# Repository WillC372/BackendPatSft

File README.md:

# Aqua Assistant AI · Backend

API REST principal de **Aqua Assistant AI**, un sistema de monitoreo de pH del agua: autenticación, perfiles de agua, mediciones, **lectura del medidor físico** (USB o Bluetooth SPP), lugares, cuidado del agua, alertas y avisos, pagos y datos oficiales.

El proyecto está en cuatro repositorios:

| Repositorio | Qué es | Dónde corre |
|---|---|---|
| [FrontendPatSft](https://github.com/WillC372/FrontendPatSft) | La aplicación web | Vercel |
| **BackendPatSft** (este) | API principal | Render |
| [AIPatSft](https://github.com/WillC372/AIPatSft) | Servicio de IA: Aqua (chat), diagnóstico, anomalías, predicción, LSTM, Isolation Forest, simulador, agente de informes, informes PDF, lectura de fotos, biblioteca normativa y traducciones | Render |
| [DBPatSft](https://github.com/WillC372/DBPatSft) | Esquema y migraciones de la base de datos | Neon (PostgreSQL) |

Los dos servicios usan la misma base de datos y la misma sesión: el servicio de IA acepta el token que entrega este backend (misma `JWT_SECRET`) y comprueba en la base que la sesión siga abierta. Entre ellos hablan por dos rutas internas protegidas con la clave compartida `INTERNAL_API_KEY`: el servicio de IA envía aquí las mediciones leídas de una foto (para que se validen y generen alertas como cualquier otra) y este backend le pide la traducción de los correos y avisos que todavía no estén en la tabla compartida.

> Frontend: carpeta [`../Frontend`](../Frontend) (repositorio [FrontendPatSft](https://github.com/WillC372/FrontendPatSft)).
>
> Requerimientos funcionales y no funcionales (historias de usuario con criterios de aceptación y MockUps): [FrontendPatSft/docs/Requerimientos.md](https://github.com/WillC372/FrontendPatSft/blob/main/docs/Requerimientos.md).

## Responsabilidades del servidor

- Registrar usuarios, iniciar y cerrar sesión, recuperar contraseñas (JWT + Argon2id).
- Guardar la **foto de perfil**: se recorta en cuadrado, se reduce a 256 px y se vuelve a codificar (se borran los metadatos, como la ubicación). Solo la ve su dueño.
- Guardar el **historial de sesiones**: cada inicio de sesión abre una sesión que agrupa todo lo que el usuario hace hasta cerrarla.
- Mantener las **cuentas de demostración** de los tres botones del inicio de sesión: Usuario, Premium y Administrador.
- Importar **datos oficiales de pH** del Servicio Geológico de EE. UU. (USGS) cada 3 horas y guardarlos aparte de las mediciones de los usuarios.
- Guardar y consultar mediciones con su origen: `REAL` (medidor), `MANUAL` o `PHOTO` (foto leída por el servicio de IA, que la envía a `POST /api/v1/internal/measurements`). El origen `SIMULATED` solo existe en las pruebas automáticas.
- Validar cada lectura (cadena de validación) y clasificarla según el perfil de agua activo.
- Hablar con el medidor por puerto serie: búsqueda, conexión, medición estabilizada, calibración y transmisión en vivo (Server-Sent Events).
- Generar **alertas** al guardar cada medición con reglas fijas: fuera del rango del perfil, **alteración del pH** y valor atípico (`alert/analysis`). El Isolation Forest y el resto de análisis están en el servicio de IA.
- **Datos oficiales del USGS en un lugar** (`place/OfficialDataService`, `POST/DELETE /api/v1/places/{id}/official-data`): carga en un lugar las lecturas reales de una estación del USGS que ya se importan (una por hora, hasta 30 días) con origen `OFFICIAL` («Dato oficial del USGS»), sin alertas ni validación de lecturas nuevas y sin repetir horas ya cargadas. Sirven para ver los análisis con días de datos reales antes de tener mediciones propias; nunca se presentan como mediciones de la persona y se pueden quitar.
- **Alteración del pH** (`PhAlterationRule`): si el pH cambia 0,5 o más frente a cualquier medición de la última hora (también con un medidor que mide cada 10 s y un cambio que crece en varios minutos), o si entra en nivel crítico, se crea la alerta «Alteración del pH en el agua» (`kind` = `PH_ALTERATION`). El mensaje dice si es peligroso según los rangos del perfil (crítico = peligroso) y qué hacer según el tipo de agua (piscina: salir del agua; acuario: los peces corren peligro; agua potable: no tomarla; riego: no regar). El aviso al celular o computador va como urgente (`Urgency: high`), queda en pantalla y vibra; la app hace sonar la alarma y Aqua lo dice en voz alta. La misma alerta no se repite en el mismo lugar durante 30 minutos (salvo que se vuelva peligrosa).
- Separar las mediciones por **lugar** (piscina, acuario, tanque...) y **compartir** un lugar con un código (rol solo ver o ver y medir).
- Guardar **otros parámetros** (cloro libre, alcalinidad, dureza cálcica, ácido cianúrico), **tratamientos**, **recordatorios** e **historial de calibraciones**.
- Enviar **avisos fuera de la app**: Web Push (cifrado RFC 8291 y VAPID RFC 8292 con el JDK, sin dependencias; las claves se crean solas en `app_keys`) y correo, para alertas y recordatorios vencidos.
- Enviar los correos y los avisos en el idioma de cada persona (`i18n/`): las traducciones están en la tabla compartida `ui_translations`, que llena el servicio de IA; lo que falta se le pide a él y, si no responde a tiempo (duerme cuando nadie lo usa), ese texto sale en español.
- Exportar mediciones a CSV. Los informes en PDF los genera el servicio de IA.

## Arquitectura

Monolito modular en capas (controlador → servicio → repositorio), organizado por módulo de negocio. Detalle y diagramas en [`docs/Architecture.md`](docs/Architecture.md). Catálogo de patrones de diseño con su función real y sus pruebas en [`docs/DesignPatterns.md`](docs/DesignPatterns.md).

```
src/main/java/com/aquaassistant/
├── AquaAssistantApplication.java
├── config/         Seguridad, CORS, OpenAPI y propiedades tipadas
├── security/       JWT, filtro de autenticación, limitador de intentos
├── common/         Errores de negocio y manejo centralizado de excepciones
├── audit/          Historial de operaciones, cada una ligada a la sesión en que se hizo
├── user/           Usuarios, autenticación, sesiones (historial), cuentas de demostración, recuperación, preferencias
├── admin/          Administración de usuarios y planes: búsqueda, plan, rol, desactivación, pagos y auditoría
├── profile/        Perfiles de agua, rangos y clasificador de pH
├── measurement/    Mediciones, cadena de validación, filtros (Specification), iterador y observadores
├── device/         Hardware: adaptadores, simulador, fábrica, máquina de estados, comandos, SSE
├── alert/          Alertas: reglas fijas al guardar cada medición (alert/analysis) y avisos
├── i18n/           Idioma de cada persona y traducción de correos y avisos (tabla compartida + servicio de IA)
├── reference/      Datos oficiales del USGS: cliente de su API (Adapter), importador programado y consulta
└── dashboard/      Consulta agregada para la pantalla de inicio
src/main/resources/
└── application.yml
src/test/resources/db/migration/   Copia de las migraciones de DBPatSft para las pruebas (java scripts/SyncMigrations.java ../DBPatSft)
docs/                        Documentación técnica
```

## Convenciones de código

- **Inglés:** nombres de clases, métodos y variables, comentarios y Javadoc, mensajes del log, claves de los datos que recibe la IA y las instrucciones (prompts) de cada capa de IA. Los prompts piden de forma explícita que la IA responda en español.
- **Español:** solo lo que ve el usuario: mensajes de error de la API, textos de informes, PDF y correos, etiquetas y resúmenes de las normas.
- **Nombres de archivo en inglés y en PascalCase**, como `MeasurementService.java`, `docs/DesignPatterns.md` o `knowledge/Guidelines.json`. Las migraciones conservan el prefijo que exige Flyway (`V1__CreateSchema.sql`).
- **Excepciones por convención de las herramientas:** `README.md`, `pom.xml`, `application.yml`, `Dockerfile`, `docker-compose.yml`, `.gitignore` y `.env.example`. Las carpetas de paquetes Java van en minúsculas, como exige Java.

Una base de datos creada antes del cambio de nombre de las migraciones necesita `flyway repair` (o actualizar `flyway_schema_history`) para registrar los nombres y sumas de verificación nuevos; una base nueva no necesita nada.

## Tecnologías

| Componente | Tecnología |
|---|---|
| Lenguaje | Java 21 |
| Framework | Spring Boot 3.4.5 (Web, Data JPA, Security, Validation, Mail, Actuator) |
| Base de datos | PostgreSQL 16 (Neon); el esquema lo aplica el repositorio DBPatSft con Flyway |
| Seguridad | JWT HS256 (jjwt 0.12.6), contraseñas con Argon2id (Bouncy Castle) |
| Hardware | jSerialComm 2.11.0 (USB serie y Bluetooth clásico SPP) |
| Documentación de la API | springdoc-openapi 2.8.6 (Swagger UI) |
| Pruebas | JUnit 5, Mockito, AssertJ, Awaitility, MockMvc, H2 (modo PostgreSQL) |

## Requisitos previos

- JDK 21 y Maven 3.9 o superior.
- PostgreSQL 16 (o Docker para levantarlo).
- Opcional: clave de la API de Anthropic, servidor SMTP y un medidor compatible (ver [`docs/Hardware.md`](docs/Hardware.md)).

## Instalación y ejecución local

1. Crea la base de datos:
   ```bash
   sudo -u postgres psql -c "CREATE USER aquasense WITH PASSWORD 'cambia-esta-clave';"
   sudo -u postgres psql -c "CREATE DATABASE aquasense OWNER aquasense;"
   ```
2. Copia `.env.example` como `.env` y completa al menos `DB_PASSWORD` y `JWT_SECRET` (32 caracteres o más).
3. Exporta las variables y arranca:
   ```bash
   set -a && source .env && set +a
   mvn spring-boot:run
   ```
   o compila el JAR:
   ```bash
   mvn -DskipTests package
   java -jar target/aqua-assistant-backend-1.0.0.jar
   ```
4. Comprueba: `http://localhost:8080/actuator/health` debe responder `{"status":"UP"}`.

Flyway crea las tablas y los cinco perfiles del sistema en el primer arranque; no hay que ejecutar SQL a mano.

### Con Docker

```bash
cp .env.example .env    # completa DB_PASSWORD y JWT_SECRET
docker compose --env-file .env up --build
```

> En Docker el backend no ve los puertos serie del equipo anfitrión. Para usar un medidor real, ejecuta el JAR directamente en el equipo donde está conectado el medidor, o comparte el dispositivo con el contenedor (`devices:` en Compose, solo en Linux).

## Variables de entorno

| Variable | Obligatoria | Descripción |
|---|---|---|
| `DB_URL`, `DB_USER`, `DB_PASSWORD` | Sí | Conexión a PostgreSQL (o `DATABASE_URL` con la cadena de Neon) |
| `AI_SERVICE_URL` | No | Dirección del servicio de IA, para traducir correos y avisos (`http://localhost:8081`) |
| `INTERNAL_API_KEY` | No | Clave que comparten este backend y el servicio de IA para sus llamadas internas (16 caracteres o más, la misma en los dos). Sin ella no se guardan las lecturas por foto |
| `FLYWAY_ENABLED` | No | `false`: el esquema lo aplica DBPatSft. Ponlo en `true` solo para crear una base local vacía con la copia de las pruebas |
| `JWT_SECRET` | Sí | Clave de firma de tokens, mínimo 32 caracteres. Sin ella el servidor no arranca |
| `PORT` | No | Puerto HTTP (8080) |
| `CORS_ORIGINS` | No | Orígenes permitidos para el frontend |
| `ADMIN_EMAIL` | No | Correo del administrador. Quien se registra o inicia sesión con él recibe un enlace en ese correo, y el rol `ADMIN` se activa **solo** cuando lo abre (así nadie puede registrarse antes con ese correo y quedarse con el rol). Requiere un canal de correo |
| `FRONTEND_ADMIN_VERIFY_URL` | No | Dirección de la pantalla que confirma el administrador (por defecto `http://localhost:5500/#/verify-admin`) |
| `API_DOCS_ENABLED` | No | `false` por defecto: Swagger UI y `/v3/api-docs` no se publican, porque el mapa completo de la API ayuda a un atacante. Ponlo en `true` solo en desarrollo |
| `CLIENT_IP_HEADER` | No | Cabecera con la dirección real del cliente que pone el proxy de delante (`CF-Connecting-IP` por defecto, la de Cloudflare en Render). Vacía: la dirección de la conexión. Fuera de Cloudflare, ponla vacía o con la cabecera de tu proxy |
| `TWILIO_ACCOUNT_SID`, `TWILIO_AUTH_TOKEN`, `TWILIO_FROM_NUMBER` | No | Alarma por SMS con Twilio ([pasos](docs/Deployment.md#alarma-por-sms-con-twilio)). Sin las tres, los SMS quedan apagados y la app lo dice |
| `MAILJET_API_KEY`, `MAILJET_SECRET_KEY`, `MAIL_FROM`, `MAIL_SENDER_NAME` | No | **Canal recomendado.** API de envío de Mailjet por HTTPS (plan gratuito de 200 correos al día; funciona aunque el puerto SMTP esté bloqueado). `MAIL_FROM` debe ser un remitente validado en Mailjet |
| `BREVO_API_KEY` | No | Alternativa: API de correo transaccional de Brevo |
| `MAIL_PROVIDER` | No | `auto` (Mailjet, Brevo o SMTP, el primero configurado), `mailjet`, `brevo`, `smtp` o `none` |
| `MAIL_HOST`, `MAIL_PORT`, `MAIL_USER`, `MAIL_PASSWORD`, `MAIL_FROM` | No | SMTP para recuperar contraseña, alternativa a Brevo. Sin ningún canal de correo, la recuperación responde 503 ("no disponible") igual para cualquier correo, y el enlace nunca se escribe en el log |
| `MAIL_LOG_RESET_LINKS` | No | **Solo desarrollo** (por defecto `false`). Con `true` y sin SMTP, el enlace de recuperación se escribe en el log para probar el flujo; al iniciar se muestra una advertencia. Con SMTP configurado se ignora. **Nunca activarlo en producción**: quien lea los registros podría tomar cuentas |
| `FRONTEND_RESET_URL` | No | URL del frontend que recibe el token de restablecimiento |
| `RATE_LIMIT_PER_MINUTE` | No | Intentos por minuto en registro, inicio de sesión y recuperación (10) |
| `DEMO_ACCOUNTS_ENABLED`, `DEMO_ACCOUNTS_PASSWORD` | No | Cuentas de demostración del inicio de sesión (`true` y `AquaAssistant-Demo-2026`). La contraseña es pública a propósito: solo abre esas cuentas limitadas |
| `REFERENCE_DATA_ENABLED`, `REFERENCE_STATIONS` | No | Importación de datos oficiales del USGS (`true`) y estaciones destacadas, separadas por comas |
| `USGS_API_KEY` | No | Clave gratuita de api.data.gov: sube el límite de solicitudes al USGS (los datos son públicos sin ella) |
| `SIMULATOR_ENABLED` | No | Simulador de medidor (`false`); solo lo encienden las pruebas automáticas |

Las claves de IA (Gemini, Groq) se configuran en el servicio de IA, no aquí.

## Documentación de la API

- Swagger UI: `http://localhost:8080/swagger-ui.html` (con `API_DOCS_ENABLED=true`; apagado por defecto)
- OpenAPI JSON: `http://localhost:8080/v3/api-docs`
- Resumen de endpoints: [`docs/Api.md`](docs/Api.md)

Todas las rutas están versionadas bajo `/api/v1`. Grupos: `auth`, `users/me` (incluye `users/me/sessions`), `profiles`, `measurements`, `places`, `treatments`, `reminders`, `calibrations`, `devices`, `alerts`, `push`, `reference`, `dashboard`, `payments` y `admin`. Las rutas `intelligence`, `knowledge`, `vision`, `reports` e `i18n` las atiende el servicio de IA.

## Autenticación y autorización

- `POST /api/v1/auth/login` devuelve un JWT. Se envía en `Authorization: Bearer <token>`.
- Duración: 8 horas, o 30 días con "Recordarme".
- `GET /auth/me` devuelve la cuenta del token y su sesión actual (inicio, vencimiento, estado). `GET /users/me` sigue devolviendo solo la cuenta.
- Cada token lleva su sesión (`sid`). Cerrar sesión termina esa sesión: su token deja de servir y la sesión queda en el historial. "Cerrar mis otras sesiones" (`POST /users/me/sessions/close-others`) cierra las de otros equipos. Cambiar la contraseña, el rol o desactivar la cuenta cierra todas.
- Contraseñas con Argon2id; tokens de recuperación de un solo uso, guardados como hash SHA-256 y con vencimiento de 30 minutos.
- Cada consulta filtra por el usuario autenticado; un usuario no puede leer ni borrar datos de otro (lo verifican las pruebas de integración).
- `/api/v1/admin/**` requiere el rol `ADMIN`. Los planes gratuito y Premium se aplican en el servidor: días de análisis histórico, horizonte de predicción y cuota diaria de IA.
- Límite de 10 intentos por minuto por dirección en registro, inicio de sesión y recuperación, con la dirección real del cliente (detrás de Cloudflare, `CF-Connecting-IP`). Además, una cuenta se bloquea 15 minutos tras 5 inicios de sesión fallidos, venga de donde venga; los intentos correctos no cuentan.

## La IA de Aqua

Está en su propio servicio, [AIPatSft](https://github.com/WillC372/AIPatSft): chat con memoria y citas, diagnóstico, anomalías, tendencias y predicción, recomendaciones con respaldo normativo, simulador de escenarios, Isolation Forest y red LSTM por lugar, agente de informes, informes en PDF, lectura de pH por foto, biblioteca normativa, consumo y costos, y las traducciones de la interfaz. Su README explica cada función.

## Historial de sesiones

Cada inicio de sesión (o registro) crea una fila en `user_sessions` con inicio, última actividad, vencimiento, si se pidió "Recordarme" y el navegador resumido ("Chrome en Windows"; no se guardan la IP ni el User-Agent completo). Cada acción del usuario (`audit_log`) se guarda con la sesión en que la hizo: mediciones, preguntas al asistente, descargas, cambios de perfil o de configuración, pagos. Al cerrar sesión, la sesión termina y su token deja de valer; al volver a entrar empieza otra. Las que vencen sin cerrar quedan como "Venció sin cerrar sesión".

- `GET /users/me/sessions`: lista con duración, estado y cuántas veces se hizo cada acción.
- `GET /users/me/sessions/{id}`: el detalle en orden.
- El administrador consulta las de cualquier cuenta (`/admin/users/{id}/sessions`).

## Cuentas de demostración

El docente revisa la app solo con los botones del inicio de sesión, así que `DemoAccounts` mantiene tres cuentas reales, una por rol del caso de estudio:

| Botón | Correo (por defecto) | Rol y plan |
|---|---|---|
| Usuario | `candow372@gmail.com` | Usuario, plan gratuito con sus límites (20 consultas de IA al día, análisis de 30 días) |
| Premium | `guifig1324@gmail.com` | Usuario, Premium sin vencimiento (200 consultas al día, hasta 365 días) |
| Administrador | `adminaqua16@gmail.com` | Administrador: cuentas, planes, pagos, consumo de IA, datos oficiales y sesiones. No mide pH |

- Los correos son buzones reales elegidos por el dueño, así llegan las alarmas, los avisos y la recuperación de contraseña. Se cambian con `DEMO_USER_EMAIL`, `DEMO_PREMIUM_EMAIL` y `DEMO_ADMIN_EMAIL`; al cambiarlos, cada cuenta conserva sus lugares, mediciones e historial.
- `GET /auth/demo-accounts` las entrega al frontend con la contraseña (`DEMO_ACCOUNTS_PASSWORD`, pública a propósito: solo abre estas cuentas compartidas).
- Pueden hacer todo lo de su rol: pagar en el sandbox de PayU, cambiar nombre, foto y contraseña, compartir lugares, eliminar la cuenta.
- Para que el botón siempre funcione, `restoreBeforeLogin` deja la cuenta como se ofrece (plan, nombre, rol y contraseña) cada vez que alguien entra con ella, y la crea otra vez si se borró.
- El administrador de demostración gestiona como cualquier administrador las cuentas de demostración y las de ejemplo (`@example.com`). Las cuentas de personas reales le aparecen enmascaradas y no puede abrirlas ni cambiarlas.
- Las direcciones viejas (`@demo.aquaassistant`) quedan desactivadas, con sus datos.

## Datos oficiales (USGS)

`ReferenceDataImporter` descarga de la API pública **Water Data OGC** del USGS (`api.waterdata.usgs.gov/ogcapi/v0`, parámetro `00400`, pH):

- Al arrancar y cada 3 horas, el último valor de cada estación que reportó pH en las últimas 24 horas (unas 470 estaciones de ríos y arroyos).
- La serie de ocho estaciones destacadas en distintos estados.
- El nombre de las estaciones con el pH más bajo y más alto.

Las lecturas se guardan 30 días en `reference_stations` y `reference_readings`, aparte de las mediciones de los usuarios. Se conserva el estado de revisión del USGS (los valores recientes son provisionales). Cada importación queda en `reference_imports`.

Si el USGS rechaza una solicitud por su límite (429) o falla un momento, se espera y se repite. Si una estación no se puede actualizar, las demás sí. `GET /reference/summary` y `GET /reference/stations/{id}/readings` alimentan la pantalla "Datos oficiales". Las pruebas usan respuestas grabadas de la API real.

## Administración

La pantalla "Administración" (solo rol `ADMIN`) muestra las cifras del sistema y permite gestionar cada cuenta.

- **Usuarios:** búsqueda por nombre o correo y filtros por rol, plan y estado, con paginación.
- **Plan:** dar Premium por 30, 90 o 365 días, o sin vencimiento, y volver a Gratuito.
- **Rol:** hacer administrador o quitar el rol. Las sesiones abiertas del usuario se cierran para que el cambio rija de inmediato.
- **Eliminar:** borrar para siempre una cuenta con todos sus datos, escribiendo su correo para confirmar. Cada usuario también puede eliminar su propia cuenta desde Configuración, con su contraseña. No se elimina la propia cuenta desde Administración, el administrador principal, el último administrador activo ni una cuenta con pagos reales aprobados.
- **Estado:** desactivar una cuenta con un motivo opcional, o reactivarla. Una cuenta desactivada no inicia sesión (403), sus tokens dejan de valer y no recibe enlaces de recuperación. Sus datos se conservan.
- **Pagos y actividad:** últimos pagos de todos los usuarios (los de prueba se distinguen de los reales) y registro de las acciones de administración.

Reglas que aplica el servidor, aunque la interfaz ya desactive el botón:

- El administrador trabaja para la empresa y **no mide el pH**: cualquier medición de una cuenta con rol `ADMIN` (a mano, con el medidor, por foto o al cargar datos del USGS) responde 403 (`Measurers.require`). El frontend le muestra otra aplicación.
- Un administrador no cambia su propio rol ni desactiva su propia cuenta.
- El administrador de `ADMIN_EMAIL` no pierde el rol ni se desactiva desde la pantalla.
- Siempre queda al menos un administrador activo.
- Una cuenta desactivada no recibe el rol de administrador.

Cada cambio queda dos veces en la auditoría: como acción del administrador y en el historial del usuario. Si hay correo configurado, el usuario recibe un aviso; el correo sale después de guardar el cambio, así que un fallo del correo no lo deshace.

## Informes en PDF

Los genera el servicio de IA ([AIPatSft](https://github.com/WillC372/AIPatSft#informes-en-pdf)).

## Pagos

Premium cuesta COP 49.900 por 30 días, con pago por periodo en PayU Latam y sin cobros automáticos. Por defecto se usa el sandbox de PayU con sus credenciales públicas de prueba: no se mueve dinero real y no hace falta registrar un comercio. El servidor activa Premium solo después de consultar la orden en PayU y comprobar estado, cuenta, valor y moneda. Lo verifiqué en vivo con un pago aprobado y otro rechazado. Los detalles, los datos de prueba y los pasos para producción están en [`docs/Payments.md`](docs/Payments.md).

## Correo

La recuperación de contraseña envía un correo con un botón y un enlace de un solo uso que vence en 30 minutos. El canal recomendado es la API de Mailjet por HTTPS (`MailjetMailChannel`); Brevo y SMTP son alternativas (patrón Strategy). Sin canal configurado la recuperación responde que no está disponible y el enlace nunca se escribe en el log, salvo en modo desarrollo (`MAIL_LOG_RESET_LINKS=true`). Los administradores ven el estado del canal y pueden enviarse un correo de prueba desde Configuración.

**Verificado con envío real (7 nov 2026):** Mailjet aceptó el correo de recuperación y lo reportó como enviado (`sent`), sin ningún enlace en el log. El enlace del correo apunta a `FRONTEND_RESET_URL`; en desarrollo es `localhost`, así que solo se abre en el mismo equipo donde corre el frontend.

## Pendientes

Las pruebas físicas con un medidor real están pendientes. Los detalles están en [`docs/PendingWork.md`](docs/PendingWork.md). La última revisión general del sistema está en [`docs/SystemReview.md`](docs/SystemReview.md).

## Integración con dispositivos

Un medidor se conecta de tres formas:

- **Al computador del usuario, desde la app publicada (Web Serial).** En Chrome o Edge, la página abre el puerto USB del medidor (o un Bluetooth emparejado como puerto serie), lee y calibra, y envía cada valor a `POST /devices/browser-readings`, que lo guarda como medición `REAL`. Es la forma de usar un medidor con el backend en la nube, que no puede ver los USB del usuario.
- **Al servidor**, cuando Aqua Assistant corre en el mismo computador del medidor: interfaz `PhMeter` con los adaptadores `AquaAssistantFirmwareAdapter` (firmware ESP32 incluido), `AtlasEzoPhAdapter` (Atlas Scientific EZO-pH por UART) y `TextMeterAdapter` (medidores de laboratorio que envían el valor como texto por USB o RS-232).
- **Por cámara**, para medidores sin cable de datos (ver `docs/Hardware.md`).

**Medidor casero.** [`hardware/Esp32PhSensor/`](https://github.com/WillC372/FrontendPatSft/tree/main/hardware/Esp32PhSensor), en FrontendPatSft, tiene todo para armar uno con un ESP32 y el módulo PH-4502C: el firmware (calibración de 1 a 3 puntos con el valor real de cada sobre, por ejemplo 6.86), el esquemático, el cableado y el plano de la baquelita, y el proyecto para simularlo en Wokwi. El firmware se compiló y se probó en el computador (31 pruebas, también en GitHub Actions); falta probarlo con el sensor físico.

El simulador de medidor solo se usa en las pruebas automáticas (`SIMULATOR_ENABLED=false` por defecto): la app publicada no muestra lecturas falsas.

**Estado:** los protocolos están probados con un puerto falso en las pruebas automáticas y en el navegador; **no se han probado con un medidor físico**. Ver [`docs/Hardware.md`](docs/Hardware.md).

## Pruebas

```bash
mvn test
```

130 pruebas automatizadas (las de la IA están en AIPatSft). Cubren:

- Patrones de diseño, algoritmos de análisis, adaptadores de hardware y máquina de estados.
- El flujo completo de la API: registro, aislamiento entre usuarios, simulador, cierre de sesión y roles.
- El historial de sesiones y las cuentas de demostración con sus límites.
- La importación de datos oficiales con respuestas grabadas del USGS.
- La alarma por alteración del pH: caída en una piscina (peligroso, salir del agua), cambio que crece con un medidor cada 10 s, consejo por tipo de agua, entrada en nivel crítico, y una sola alerta para varias lecturas seguidas.
- Las rutas internas con la clave compartida y la traducción de correos: primero la tabla compartida, luego el servicio de IA, y en español si no responde.
- Los siete patrones vistos en clase con su función: las familias de medidor (Abstract Factory), los avisos (Bridge) y sus canales decorados (Decorator), además de Factory Method, Adapter, Facade y Proxy.
- Los tres botones de acceso: la cuenta vuelve a su estado al entrar, y el administrador de demostración solo abre cuentas de demostración o de ejemplo.
- Que el administrador no pueda registrar mediciones (403) y que una medición crítica haga sonar la alarma aunque no haya mediciones en la última hora.

Se ejecutan con H2 en modo PostgreSQL y una copia de las migraciones de DBPatSft (`java scripts/SyncMigrations.java ../DBPatSft` la actualiza); para correrlas contra PostgreSQL real:

```bash
mvn test -Dspring.datasource.url=jdbc:postgresql://localhost:5432/aquasense_test \
  -Dspring.datasource.username=aquasense -Dspring.datasource.password=TU_CLAVE
```

GitHub Actions las corre en cada cambio de `main` (`.github/workflows/Tests.yml`). Último resultado (20 nov 2026, con BackendPatSft#12): 130/130 aprobadas, en local y en GitHub Actions.

## Despliegue

Publicado en **Render** (backend y servicio de IA con Docker, plan gratuito), **Neon** (PostgreSQL, esquema aplicado por DBPatSft) y **Vercel** (frontend). La guía paso a paso está en [`docs/Deployment.md`](docs/Deployment.md).

| Parte | Dirección |
|---|---|
| Aplicación | https://aquaassistantai.vercel.app |
| API | https://aquasense-backend-willc372.onrender.com/api/v1 (salud: `/actuator/health`; para pings que la mantengan despierta: `/actuator/health/liveness`) |
| Servicio de IA | https://aquasense-ai-willc372.onrender.com/api/v1 ([AIPatSft](https://github.com/WillC372/AIPatSft)) |

Verificado en producción: el formulario de registro y el de medición de la página de Vercel llaman a la API de Render y guardan en Neon; CORS acepta solo el dominio de Vercel (otro origen recibe 403); el correo está configurado.

- `render.yaml` crea el servicio con su verificación de salud (`/actuator/health`), genera `JWT_SECRET` (cópiala al servicio de IA) y fija las direcciones del frontend y del servicio de IA. Las claves (base de datos, `INTERNAL_API_KEY` y correo) se escriben en el panel de Render, nunca en el repositorio.
- La base se configura con una sola variable, `DATABASE_URL`, con la cadena que entrega Neon (`postgresql://usuario:clave@host/db?sslmode=require`).
- **Se duerme cuando nadie la usa:** Render apaga la instancia gratuita tras 15 minutos sin uso; así alcanzan las 750 horas del mes para este backend y el servicio de IA. `.github/workflows/WakeUp.yml` la mantiene despierta junto con el servicio de IA (modo `always`, desde el 20 nov 2026) o, con la variable `KEEP_AWAKE_MODE=3h` de GitHub, la despierta cada 3 horas para enviar recordatorios e importar los datos del USGS; dormida, la primera visita tarda alrededor de un minuto. Con `KEEP_AWAKE=true` en Render se mantiene despierta ([detalle](docs/Deployment.md#el-backend-se-duerme-cuando-nadie-lo-usa)).
- **Memoria que se limpia sola:** los intentos de inicio de sesión viejos se borran solos. En la base, los enlaces de recuperación y verificación usados o vencidos hace más de un día se borran cada 6 horas.
- El `Dockerfile` está ajustado a instancias de 512 MB. Los informes PDF y los modelos de IA, lo que más memoria usaba, ahora corren en el servicio de IA.

Un backend en la nube no puede leer un medidor conectado a tu computador. Para lecturas físicas, el backend debe correr en el equipo donde está conectado el medidor.

## Solución de problemas

| Síntoma | Causa y solución |
|---|---|
| La primera visita tarda alrededor de un minuto | Render apagó la instancia por inactividad (se deja dormir para ahorrar horas). Espera el aviso «Activando el servidor...»; para una presentación, agrega `KEEP_AWAKE=true` en Render ([detalle](docs/Deployment.md#el-backend-se-duerme-cuando-nadie-lo-usa)). |
| `JWT_SECRET must be set...` al arrancar | Define `JWT_SECRET` con 32 caracteres o más |
| `Connection refused` a PostgreSQL | Verifica que el servicio esté activo y los valores de `DB_*` |
| El frontend muestra "No se pudo conectar con el servidor" | Backend apagado, o el origen del frontend no está en `CORS_ORIGINS` |
| No aparece el puerto del medidor | Revisa el cable y el controlador USB. En Linux agrega tu usuario al grupo `dialout`. Para Bluetooth, empareja primero desde el sistema |
| Una foto se lee pero no se guarda | `INTERNAL_API_KEY` falta o no es la misma en el backend y en el servicio de IA |
| Tras actualizar el servidor, todos deben volver a iniciar sesión | Los tokens emitidos antes del historial de sesiones no llevan sesión (`sid`) y ya no valen; ocurre una sola vez |
| "Datos oficiales" dice que la última actualización falló | El USGS no respondió o limitó las solicitudes; se muestran los datos anteriores y se reintenta en 3 horas. `USGS_API_KEY` sube el límite |
| "La recuperación de contraseña no está disponible" | No hay canal de correo: define `MAILJET_API_KEY`, `MAILJET_SECRET_KEY` y `MAIL_FROM` (o Brevo o SMTP). Solo en desarrollo puedes usar `MAIL_LOG_RESET_LINKS=true` y copiar el enlace del log |

## Licencia

Proyecto académico de Patrones de Software. Sin licencia de uso definida por el autor.

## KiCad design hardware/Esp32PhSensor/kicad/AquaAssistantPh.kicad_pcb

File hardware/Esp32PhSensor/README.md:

# Medidor de pH casero: ESP32 + PH-4502C

Firmware y planos para armar un medidor de pH económico que la app lee por USB (o Bluetooth) con el tipo de medidor **«Firmware Aqua Assistant (ESP32)»**.

> Estado: el firmware se compiló y se probó en un computador con una capa que imita a Arduino (31 pruebas, `tools/FirmwareTest.cpp`) y se puede simular en Wokwi. **Todavía no se ha probado con el sensor físico.**

## Proyecto KiCad y documentación (cuatro vistas del mismo circuito)

El circuito también está como proyecto de **KiCad 7** en [`kicad/`](kicad/) (ábrelo con `AquaAssistantPh.kicad_pro`), con una PCB de 2 capas de 80 × 44 mm en la que el ESP32 se enchufa en dos zócalos 1×19. En [`documentacion/`](documentacion/) están las cuatro representaciones, exportadas desde ese proyecto, y el resumen en [`Documentacion-Medidor-pH.pdf`](documentacion/Documentacion-Medidor-pH.pdf):

| Vista | Archivos editables / exportables |
|---|---|
| 1. Esquemático | `kicad/AquaAssistantPh.kicad_sch` · PDF y SVG vectoriales · netlist `AquaAssistantPh.net` |
| 2. Vista 3D de la PCB | `AquaAssistantPh-STEP.zip` (STEP: FreeCAD, Fusion 360, SolidWorks) · `AquaAssistantPh.glb` (Blender, Visor 3D) · 4 renders |
| 3. Montaje en protoboard | `Protoboard.svg` (Inkscape, Illustrator) · `protoboard.json` (conexiones) · PNG |
| 4. Layout de PCB | `kicad/AquaAssistantPh.kicad_pcb` · hoja del layout (SVG/PNG) · PDF por capa · Gerber + taladros (`AquaAssistantPh-Gerber.zip`) · BOM |

- **Mismo circuito en todas:** [`Consistencia.md`](documentacion/Consistencia.md) compara red por red la netlist del esquemático, los pads de la PCB y las conexiones de la protoboard: coinciden. La vista 3D se genera desde el mismo archivo de PCB.
- **Reglas de diseño (DRC) de KiCad:** 0 errores, 0 pads sin conectar.
- Antes de mandar a fabricar la PCB, confirma con tu ESP32 que las filas de pines están a 25,4 mm (es lo que usa el diseño) y el orden de pines de tu PH-4502C.
- La carpeta [`planos/`](planos/) es la versión para baquelita perforada (sin fabricar PCB), con el mismo circuito.

## Piezas

| Ref. | Pieza | Cant. |
|---|---|---|
| U1 | ESP32 de 38 pines con USB-C (módulo ESP-32) | 1 |
| U2 | Módulo PH-4502C | 1 |
| — | Sonda de pH E201 con conector BNC | 1 |
| R1, R2 | Resistencia 20 kΩ, 1/4 W | 2 |
| J1 | Espadín hembra 1×19 | 2 |
| J2 | Espadín hembra 1×3 | 1 |
| — | Baquelita perforada de al menos 24×24 huecos | 1 |
| — | Cables Dupont macho-hembra | 3 |
| — | Sobres de calibración pH 6.86 y 4.00 (opcional 9.18) y agua destilada | — |

## Conexiones

| PH-4502C | Va a | Nota |
|---|---|---|
| V+ | 5V del ESP32 | Alimentación desde el USB |
| G | GND del ESP32 | Basta uno de los dos G |
| Po | R1 → G34 del ESP32, y R2 de G34 a GND | El divisor deja la señal a la mitad (máx. 2,5 V) |
| Do, To | sin conectar | |

Planos completos en [`planos/`](planos/): esquemático, cableado y baquelita (vista superior e inferior), también en un PDF para imprimir.

## Comandos (9600 baudios, una línea por comando)

| Comando | Respuesta |
|---|---|
| `PING` | `PONG AQUA-ASSISTANT-PH-001` |
| `READ` | `PH:7.02;T:NA`, o `ERR:NO_SIGNAL` si no hay sensor, o `ERR:OUT_OF_RANGE` |
| `CAL:MID:6.86` | `OK` (valor entre 6.00 y 8.00) |
| `CAL:LOW:4.00` | `OK` (entre 2.00 y 5.50); `ERR:SAME_AS_MID` si la sonda está en el sobre equivocado |
| `CAL:HIGH:9.18` | `OK` (entre 8.50 y 12.00) |
| `CAL:CLEAR` | `OK` y vuelve a los valores de fábrica |
| `STATUS` | `MV:1251.3;MID:1300.0@6.86;LOW:1560.0@4.00;HIGH:-` |

Cada lectura toma 21 muestras y descarta las 5 más altas y las 5 más bajas. La calibración usa el valor escrito en el comando, así que sirven los sobres de 6.86 y 9.18. Se guarda en la memoria del ESP32 y no se pierde al desconectarlo.

## Cargar el firmware

1. Instala **Arduino IDE 2** y, en *Herramientas → Placa → Gestor de placas*, el paquete **esp32** de Espressif.
2. Abre `Esp32PhSensor.ino`. Placa: **ESP32 Dev Module**. Puerto: el que aparece al conectar el USB-C.
3. Si Windows no reconoce la placa, instala el controlador del chip USB que tenga impreso (CP210x, CH340 o CH9102).
4. Pulsa **Subir**. En el *Monitor serie* (9600 baudios, «Nueva línea») escribe `PING`: debe responder `PONG AQUA-ASSISTANT-PH-001`.

## Calibrar

En la app: **Conexión → «Medidor conectado a este equipo»**, elige el tipo «Firmware Aqua Assistant (ESP32)», pulsa **Conectar** y luego **Calibrar**. En la ventana, cambia «Valor del buffer» por el número de tu sobre:

1. Sonda en el sobre **6.86**, espera 1 minuto y calibra el punto **Medio** con el valor `6.86`.
2. Enjuaga la sonda con agua destilada y sécala con toques suaves.
3. Sonda en el sobre **4.00**, espera y calibra el punto **Bajo** con `4.00`.
4. Opcional: sobre **9.18**, punto **Alto** con `9.18`.

Antes de calibrar, gira la perilla «ajuste pH 7» del PH-4502C para que en el sobre 6.86 `STATUS` muestre cerca de 1250 mV.

## Simular en Wokwi (sin el sensor)

1. Abre https://wokwi.com/projects/new/esp32.
2. Reemplaza el contenido de `sketch.ino` por [`wokwi/sketch.ino`](wokwi/sketch.ino).
3. En la pestaña `diagram.json`, reemplaza todo por [`wokwi/diagram.json`](wokwi/diagram.json). Aparece un potenciómetro conectado a G34 que hace de sensor.
4. Pulsa ▶. En el monitor serie escribe `PING`, `READ`, `STATUS`. Gira el potenciómetro (clic y arrastrar) y vuelve a pedir `READ`.
5. Prueba la calibración: deja el potenciómetro en una posición, envía `CAL:MID:6.86`; súbelo un poco, envía `CAL:LOW:4.00`; ponlo en medio y pide `READ`.

Sin calibrar, el potenciómetro marca pH 7 cerca de un 38 % de su recorrido; fuera de aproximadamente 19 %–57 % responde `ERR:OUT_OF_RANGE`, porque esa parte equivale a pH por debajo de 0 o por encima de 14.

## Pruebas en el computador

```bash
g++ -std=c++17 -Wall -Wextra -I tools/shim -x c++ tools/FirmwareTest.cpp -o fwtest && ./fwtest
```

`tools/shim/` imita las funciones de Arduino que usa el firmware (lectura analógica, memoria y puerto serie). El flujo `.github/workflows/Firmware.yml` corre estas pruebas en cada cambio de esta carpeta.

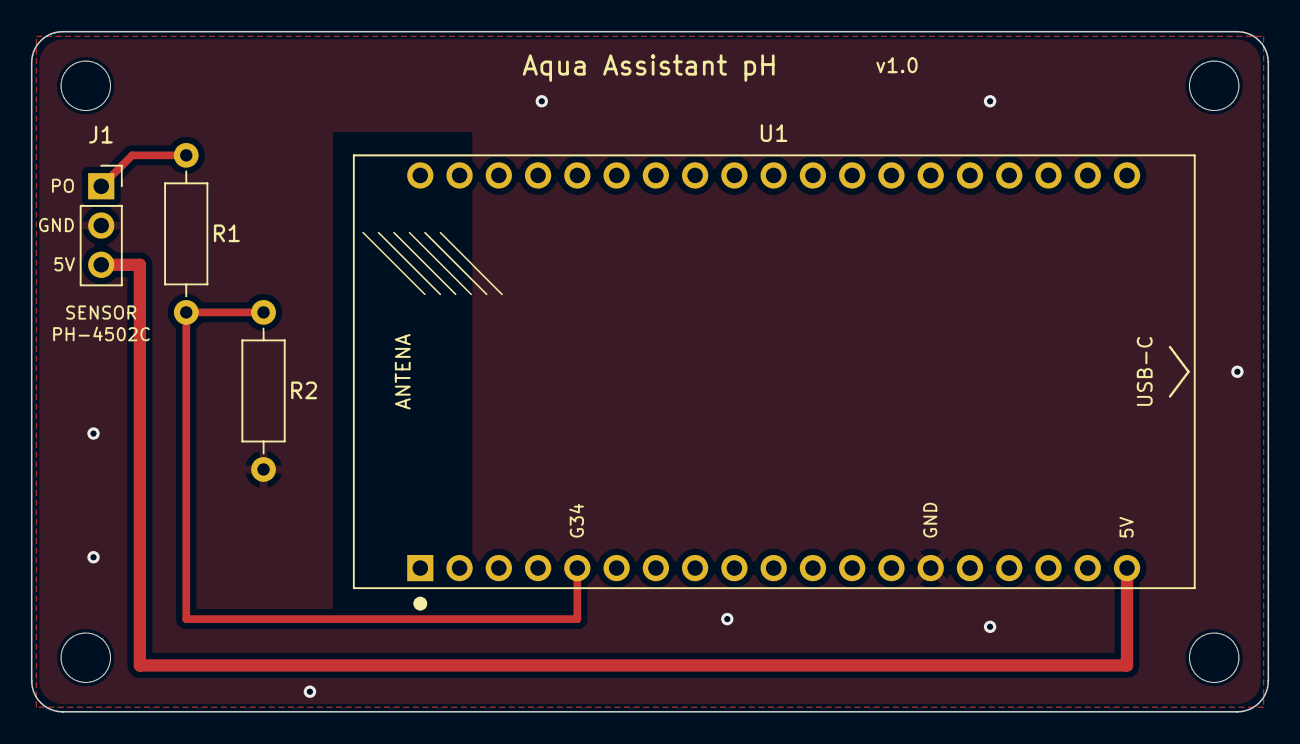
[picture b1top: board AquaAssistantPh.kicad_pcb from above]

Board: 2 copper layers, 80.0 x 44.0 mm, 8 parts (0 on the bottom side), 4 nets.

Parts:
H1, H2, H3, H4: M3; MountingHole_3.2mm_M3
J1: SENSOR; PinSocket_1x03_P2.54mm_Vertical
R1, R2: 20k; R_Axial_DIN0207_L6.3mm_D2.5mm_P10.16mm_Horizontal
U1: ESP32_DevKit_38P; ESP32_DevKit_38P_Socket

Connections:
+5V: J1.3, U1.19 (5V)
/PH_ADC: R1.2, R2.1, U1.5 (G34)
/PH_OUT: J1.1, R1.1
GND: J1.2, R2.2, U1.14 (GND)
